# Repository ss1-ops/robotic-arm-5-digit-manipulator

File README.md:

# BCN3D Moveo Robotic Arm

Client-commissioned 6-DOF robotic arm (BCN3D Moveo base) with custom Aero Hand tendon-driven gripper. End goal: autonomous pick-and-place using computer vision on a Raspberry Pi running ROS 2 Jazzy, with low-level control on ESP32-S3 (micro-ROS).

**Current status (2026):** Transitioning from Arduino Uno R4 to ESP32-S3. Basic joint control, IK, and manual GUI working. Vision bring-up and full integration in progress. Aero Hand partially assembled (3 fingers functional).

## Quick Links
- [Current Build Status & Architecture](docs/arm-build-progress.md)
- [ROS 2 Setup on armpi (live inventory)](https://github.com/ss1-ops/robotic-arm-5-digit-manipulator/blob/main/docs/arm-build-progress.md) (see also Obsidian notes)
- [Aero Hand Gripper](gripper/aero-hand-open/) — full open-source tendon-driven hand (7 DoF, 3D-printed, ROS 2 + SDK + firmware)
- [Firmware (ESP32-S3)](firmware/esp32s3-arm-controller/)
- [Software / ROS 2 + GUI + Vision](software/)
- [Hardware / CAD](hardware/)
- [Original BCN3D Reference](reference/bcn3d-moveo/) (attribution + source files)

## Project Structure (Cleaned for Maintainability)
```
.
├── README.md
├── LICENSE
├── .gitattributes
├── docs/
│   └── arm-build-progress.md          # Detailed pinouts, commands, issues, future plans
├── hardware/
│   ├── cad/                           # Custom + reference CAD (STEP, STL, F3D, 3MF)
│   └── enclosure/                     # Custom platform/enclosure designs
├── firmware/
│   ├── esp32s3-arm-controller/        # Active micro-ROS target firmware
│   └── legacy-tests/                  # Earlier Arduino sketches
├── software/
│   ├── mac-gui/                       # macOS desktop GUI + ROS 2 nodes for manual control
│   ├── ros/                           # ROS 2 nodes, publishers, launchers
│   └── vision/                        # Stereo calibration, hand-eye, IBVS, object approach
├── gripper/
│   └── aero-hand-open/                # Full Aero Hand Open (tendon-driven EE)
│       ├── firmware/, hardware/ (CAD+PCB), ros2/, sdk/, ...
├── reference/
│   └── bcn3d-moveo/                   # Original open-source BCN3D Moveo mechanical files (parts 1+2)
├── urdf/                              # Robot description
└── assets/                            # Footage, images
```

## Current Capabilities
- ROS 2 Jazzy on Raspberry Pi (armpi.local)
- Joint control via forward_position_controller + serial bridge to stepper drivers
- Smooth IK + coordinated motion
- Manual Mac GUI for testing (joint sliders, sequences)
- Stereo vision pipeline (calibration, depth, object approach)
- Aero Hand gripper (tendon-driven, 7 servos, partial assembly + control)

See `docs/arm-build-progress.md` for pinouts, exact launch commands, known issues, and detailed roadmap (ESP32-S3 migration, PCA9685 for gripper, eye-in-hand CV, homing, etc.).

## Getting Started (High Level)
1. On the Pi: source ROS 2, launch description + controller.
2. Run serial bridge or micro-ROS agent.
3. Use Mac GUI or `ros2 topic pub` for commands.
4. For gripper: see `gripper/aero-hand-open/` (has its own SDK, ROS2 packages, firmware examples).

Full live setup details are in the build progress doc and the armpi SSH inventory.

## Sub-Projects & Highlights
- **Aero Hand Open** (`gripper/aero-hand-open/`): Professional open-source 7-DoF tendon-driven hand. Includes hardware (CAD, PCB, BOM), firmware, Python SDK, ROS 2 integration, simulation, RL tools. See its README for features, assembly, and shop links.
- **Vision & CV**: Hand-eye calibration, IBVS servo, stereo depth for pick-and-place. Eye-in-hand mount planned.
- **Firmware Evolution**: Moving to ESP32-S3 for native micro-ROS, OTA, more I/O (PCA9685 for servos, IMUs).

## License
MIT (see LICENSE). Sub-components may have their own licenses (e.g., Aero Hand, original BCN3D).

## Attribution
Base arm mechanics from the excellent open-source [BCN3D Moveo](https://github.com/BCN3D/BCN3D-Moveo) project. Custom work by Sam Snyder (automation, controls, integration, Aero Hand adaptation, vision).

For the absolute latest status, wiring, or Pi inventory, see the linked Obsidian notes or run live exploration on `armpi`.

---

**Active project** — contributions and questions welcome via issues or the linked Discord/community channels in the Aero Hand sub-project.

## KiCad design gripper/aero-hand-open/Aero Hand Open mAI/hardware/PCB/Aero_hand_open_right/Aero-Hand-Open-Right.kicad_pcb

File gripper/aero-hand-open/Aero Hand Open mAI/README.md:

<p align="center">

  <!--  -->

</p>

Aero Hand Open is an **open-source**, **tendon-driven** robotic hand designed and developed by TetherIA for dexterous manipulation research. Unlike expensive proprietary solutions, this hand focuses on **simplicity**, **reliability**, and **accessibility** by using standard 3D printing and off-the-shelf electronic components.

Each joint is optimized for mechanical efficiency through tendon actuation, enabling smooth and natural motion while maintaining a **lightweight** and **compact** design, making it perfect for research labs, educational institutions, and robotics enthusiasts who need an **affordable** yet **capable** manipulation platform.

> **📚 Learn More:** https://tetheria.github.io/aero-hand-open/   
> **🛒 Shop:** https://shop.tetheria.ai/

# Aero Hand Open features
- 7 DoFs robotic hand with 5 fingers (16 joints in total)
- Tendon-driven architecture for smooth and natural motion
- Fully 3D-printed structure, modular and easy to assemble
- Lightweight design — **389 g**
- Affordable — complete kit for **$314 USD**
- Open-source hardware and firmware
- Independent Python SDK, and compatible with ESP32 and ROS2 systems

# Table of Contents
- [Aero Hand Open features](#aero-hand-open-features)
- [Overview](#overview)
- [Resources](#resources)
  - [Bill of Materials (BOM)](#bill-of-materials-bom)
  - [CAD Files and 3D Models](#cad-files-and-3d-models)
  - [Assembly Guide](#assembly-guide)
  - [PCB Design](#pcb-design)
  - [Hardware Setup](#hardware-setup)
  - [Software SDK](#software-sdk)
  - [ROS2 and Teleoperation](#ros2-and-teleoperation)
  - [Simulation](#simulation)
  - [Reinforcement Learning](#reinforcement-learning-tools)
- [Getting help](#Getting-help)
- [License — TL;DR](#license--tldr)
- [Disclaimer](#disclaimer)
- [Project Updates & Community](#project-updates--community)
  - [Updates History](#updates-history)
  - [FAQ](#faq)
  - [Contact](#contact)

# Overview

# Resources
## Bill of Materials (BOM)
The complete list of components required to build Aero Hand Open can be found here:

 [👉 Aero Hand Open – Bill of Materials](./hardware/Assembly/BOM.csv)

This document includes all mechanical, electronic, and printed parts — such as motors, tendons, bearings, fasteners, and 3D-printed components.

Each item is listed with its part number, vendor, quantity, and estimated cost to help you easily source or substitute parts.

## CAD Files and 3D Models
STEP files and one click print files can be found here:

[👉 Aero Hand Open – CAD](./hardware/CAD/).

[👉 Aero Hand Open – Onshape Link](https://cad.onshape.com/documents/afc7e0ca7eb6d412ec8771f8/w/bc4d7e45e17e23d622d2bad2/e/c711982b7882da925263fb55?renderMode=0&uiState=6914cef580110c73012e8166)

All parts are printed on a Bambu X1C, 0.4mm nozzle, 0.2mm layer height, tree support enabled, select support on build plate only checkbox. We recommend keeping the same print orientation and settings. The print orientation will minimize supports and optimize surface tolerances/smoothness for interfacing components.

## Assembly Guide
The step-by-step assembly instructions for Aero Hand Open are provided in the following document:

[👉 Aero Hand Open – Assembly Guide](https://docs.tetheria.ai/docs/assembly)

This guide covers the entire build process, from mounting the actuators to routing the tendons and connecting the electronics. Each finger module can be assembled independently and attached to the palm afterward, allowing easier maintenance and quick replacement.

## PCB Design
All design files - including Gerber files, KiCad project files, BOM, and CPL - are available in [PCB folder](./hardware/PCB/).

Referring to [PCB doc](https://docs.tetheria.ai/docs/pcb) for more technical details.

## Hardware Setup

Please refer to [hardware_setup](https://docs.tetheria.ai/docs/hardware_setup) doc 

## Software SDK
Please refer to [`sdk/README.md`](sdk/README.md) and [sdk](https://docs.tetheria.ai/docs/sdk) doc

### Sequencing Demo
The Sequencing Demo demonstrates how different finger motions can be combined into continuous, pre-defined sequences.

This script enables users to perform complex gestures — such as pinching, opening the palm, or making a peace sign — by automatically coordinating joint movements in a timed sequence.

You can find the example code in the SDK example folder. 

👉 [`sdk/examples/`](sdk/examples)

Once the SDK is installed and the serial port has been configured, you can run any of the example scripts directly using Python as follows:

```bash
python run_sequence.py
```
[🎥 Watch the demo](assets/sequence_square.mp4)

## ROS2 and Teleoperation
The Aero Hand Open integrates seamlessly with ROS2 **humble** for advanced robotics applications.

Refer to the [ROS2](https://docs.tetheria.ai/docs/ros2) doc and [`ros2/`](./ros2/) folder for complete setup instructions and source code.

## Simulation

We provide high-fidelity simulation models for the **Tetheria Aero Hand Open**.

**Currently Supported**
- **MuJoCo**

Support for additional simulation platforms is under active development and will be released in future updates.  
Refer to the [RL and Sim](https://docs.tetheria.ai/docs/hand_sim) documentation and the [`sim_rl/simulation/`](./sim_rl/simulation/) directory for detailed explanations and model files.

## Reinforcement Learning Tools

We offer reinforcement learning tools built on top of state-of-the-art frameworks such as **mujoco_playground**, enabling users to train custom policies for the Aero Hand Open with minimal effort.

Refer to the [RL and Sim](https://docs.tetheria.ai/docs/hand_sim) documentation and the [`sim_rl/mujoco_playground/`](./sim_rl/mujoco_playground/) directory for full setup instructions and training procedures.  
An example of deploying trained policies in ROS is also provided in the [`ros2/`](./ros2/) directory.

# Getting help

**GitHub Issues** – Bugs + feature requests only.

**GitHub Discussions** –
- Build / electronics / mechanical help
- SDK / ROS2 / sim/RL "how do I…"
- Design proposals and feedback

**Discord** –
- Quick questions, live debugging, voice/screen‑share
- Social chat, lab intros, "I printed my first hand!"
- Live events and office hours

# License — TL;DR

- You **can** integrate Aero Hand units you purchase from TetherIA into **commercial robots and products** you sell.
- **Software (firmware & SDK):** Apache-2.0 — commercial use OK (with notices).
- **Design files (CAD/STEP/STL, drawings, BOM, docs):** CC BY‑NC‑SA 4.0 — **non‑commercial** only; derivatives must use the same license with attribution.
- Want to **manufacture/print parts** or **make your own hands** from our design files for commercial use (spares, kits, or clones)? → **Commercial manufacturing license required**.
- **Commercial licensing & volume buys:** see **LICENSE.md** (or email us at contact@tetheria.ai).

See [**LICENSE.md**](LICENSE.md) for definitions, examples, and contact details.

© 2025 TetherIA Inc. All rights reserved.

# Disclaimer
Aero Hand Open is an open-source research prototype intended for educational and experimental purposes only.

While every effort has been made to ensure build accuracy and functionality, this design has not been validated for prolonged or heavy-duty use.

Users should exercise caution when assembling, operating, or modifying this device. TetherIA Inc. and its contributors shall not be held liable for any personal injury, property damage, or other losses resulting from the use, misuse, or modification of this design. By using this project, you acknowledge and accept full responsibility for any associated risks.

Important Notes:
- 3D-printed parts may exhibit tolerance variations depending on printer and material settings.
- The tendon-driven mechanism requires regular tension adjustment to maintain consistent motion.
- Overloading the joints or applying excessive torque may cause mechanical deformation or servo damage.
- This project is provided as is, without any warranty or guarantee of fitness for a particular purpose.

We encourage the community to share improvements, feedback, and modifications through pull requests or GitHub discussions.

Your contributions will help make Aero Hand Open more reliable and versatile for the entire robotics community.

# Project Updates & Community
## Updates History
See [RELEASE_NOTES.md](RELEASE_NOTES.md) for details.

## FAQ
Q1: Can I modify and redistribute the Aero Hand Open design?

A: Yes, as long as it complies with the CC BY-NC-SA 4.0 license (non-commercial, attribution required, share alike).

Q2: What 3D printer and material do you recommend?

A: Any FDM printer with a ≥200×200 mm bed. PLA works best for strength and dimensional accuracy.

More questions please refer to our [online documentation](https://docs.tetheria.ai/docs/hardware_faq) 

## Contact
For questions, feedback, or collaboration inquiries, please reach out to us through the following channels:

 🛒 Shop: [Aero Hand Open – TetherIA Store](https://shop.tetheria.ai/) 

 📚 Docs: [TetherIA Docs](https://docs.tetheria.ai/)

 📧 Email: support@tetheria.ai

 🌐 Website: [tetheria.ai](http://tetheria.ai)

 🐙 GitHub: [TetherIA](https://github.com/TetherIA)

 💬 Discord: [TetherIA Discord Channel](http://discord.gg/ZQKWK7NebQ)

  🐦 X/Twitter: [TetherIA X/Twitter Account](https://x.com/TetherIA_ai)

  📺 YouTube: [TetherIA YouTube Account](https://www.youtube.com/@TetherIA_ai)

  💼 LinkedIn: [TetherIA LinkedIn Account](https://www.linkedin.com/company/tetheria/)

We welcome discussions, contributions, and new ideas from the community.

If you have improvements to the design, firmware, or control software, feel free to open a Pull Request or start a Discussion on GitHub.

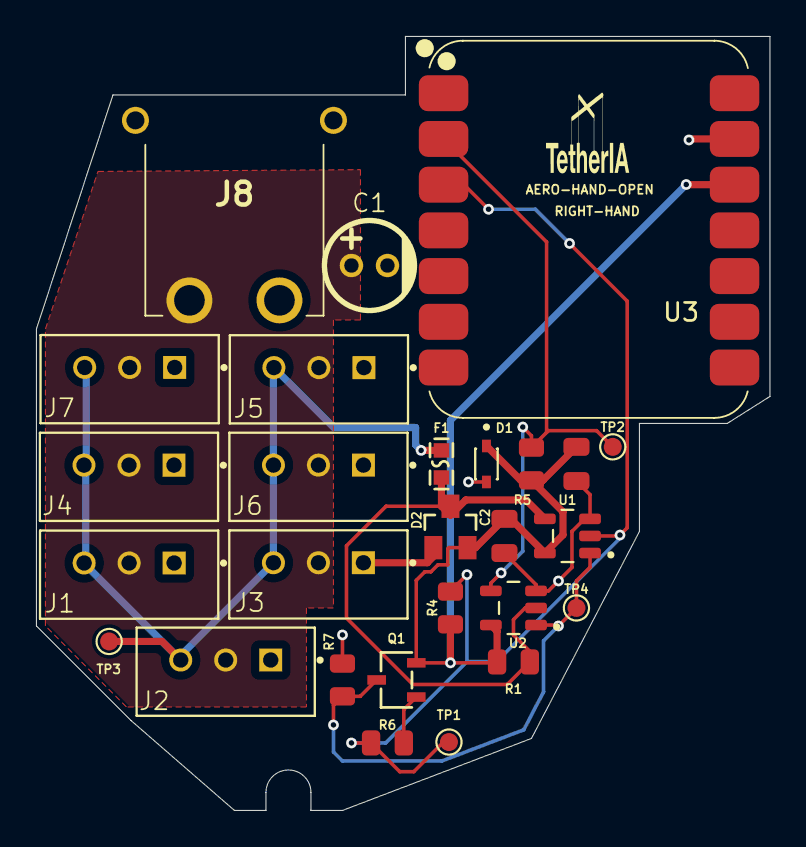
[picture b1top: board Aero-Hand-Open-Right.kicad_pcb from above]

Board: 2 copper layers, 40.7 x 43.0 mm, 27 parts (1 on the bottom side), 9 nets.

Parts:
C1: 100uF; CAP-TH_BD5.0-P2.00-D0.8-FD
C2, C3: 0.1uF; C_0805
D1: BZT52B5V1S; DIO_BZT52B5V1S
D2: BAT54S; bat4s kl4
F1: BSMD0603-010-24V; F0603
J1, J2, J3, J4, J5, J6, J7: 22-03-5035; MOLEX_22-03-5035
J8: XT30PW-M; XT30PWM
Q1: MMBT2907A; transistor-SOT-23-3_L3.0-W1.7-P0.95-LS2.9-BR
R1, R4, R5: 10K; R_0805
R6: 1K; R_0805
R7: 3.3K; R_0805
TP1, TP2, TP3, TP4: TestPoint; TestPoint_Pad_D1.0mm
U1: SN74LVC1G126DBVR
U2: SN74LVC1G125DBVR
U3: XIAO-ESP32-S3-DIP; XIAO-ESP32S3-SMD

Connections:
DC6V: C1.1, J1.2, J2.2, J3.2, J4.2, J5.2, J6.2, J7.2, J8.2
GND: C1.2, C2.1, C3.1, D1.A, D2.1, J1.1, J2.1, J3.1, J4.1, J5.1, J6.1, J7.1, J8.1, J8.3, J8.4, R7.2, U1.3 (GND), U2.3 (GND), U3.13 (GND)
unnamed: Q1.1 (B), R6.2
Servo_DATA: D2.3, F1.2, R1.1, U1.4 (Y), U2.2 (A)
Servo_DATA_IN: F1.1, J1.3, J2.3, J3.3, J4.3, J5.3, J6.3, J7.3, TP3.1
Servo_RXD: R4.2, R6.1, TP1.1, U1.2 (A), U3.3 (GPIO3/A2/D2)
Servo_RXEN: Q1.3 (C), R7.1, TP4.1, U1.1 (OE), U2.1 (~OE)
Servo_TXD: R5.2, TP2.1, U2.4 (Y), U3.2 (GPIO2/A1/D1)
VCC: C2.2, C3.2, D1.C, D2.2, Q1.2 (E), R1.2, R4.1, R5.1, U1.5 (VDD), U2.5 (VCC), U3.12 (VCC_3V3)

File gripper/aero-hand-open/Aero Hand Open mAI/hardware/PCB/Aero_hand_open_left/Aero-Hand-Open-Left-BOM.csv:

Comment,Quantity,Designator,Footprint,JLCPCB Part,Link,,,,,,,,,,,,,,
100uF,1,C1,CAP-TH_BD5.0-P2.00-D0.8-FD,C47873,https://jlcpcb.com/partdetail/48879-KM107M025D11RR0VH2FP0/C47873,,,,,,,,,,,,,,
100nF,2,"C2,C3",C_0805,C520082,https://jlcpcb.com/partdetail/YAGEO-CC0805JRX7R7BB104/C520082,,,,,,,,,,,,,,
BZT52B5V1S,1,D1,DIO_BZT52B5V1S,C5261067,https://jlcpcb.com/partdetail/HXYMOSFET-BZT52B5V1S/C5261067,,,,,,,,,,,,,,
BAT54S,1,D2,BAT4S KL4,C8592,https://jlcpcb.com/partdetail/9087-BAT54SKL4/C8592,,,,,,,,,,,,,,
BSMD0603-010-24V,1,F1,F0603,C883089,https://jlcpcb.com/partdetail/BHFUSE-BSMD0603_01024V/C883089,,,,,,,,,,,,,,
MOLEX CONNECTOR,7,"J1,J2,J3,J4,J5,J6,J7",MOLEX_22-03-5035,C5458299,https://jlcpcb.com/partdetail/MOLEX-0022035053/C5458299,,,,,,,,,,,,,,
XT30PW-M,1,J8,XT30PWM,C431092,https://jlcpcb.com/partdetail/Changzhou_AmassElec-XT30PW_M30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,,,,,,,,,,,,,,
MMBT2907A,1,Q1,Transistor-SOT-23-3_L3.0-W1.7-P0.95-LS2.9-BR,C305431,https://jlcpcb.com/partdetail/Foshan_Blue_RocketElec-MMBT290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,,,,,,,,,,,,,,
10K,3,"R1,R4,R5",R_0805,C702829,https://jlcpcb.com/partdetail/HKR_Hong_Kong_Resistors-RCT051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,,,,,,,,,,,,,,
1K,1,R6,R_0805,C702831,https://jlcpcb.com/partdetail/HKR_Hong_Kong_Resistors-RCT051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,,,,,,,,,,,,,,
3.3K,1,R7,R_0805,C702834,https://jlcpcb.com/partdetail/HKR_Hong_Kong_Resistors-RCT053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,,,,,,,,,,,,,,
SN74LVC1G126DBVR,1,U1,SN74LVC1G126DBVR,C7834,https://jlcpcb.com/partdetail/TexasInstruments-TISN74LVC1G12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,,,,,,,,,,,,,,
SN74LVC1G125DBVR,1,U2,SN74LVC1G125DBVR,C23654,https://jlcpcb.com/partdetail/TexasInstruments-TISN74LVC1G12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,,,,,,,,,,,,,,

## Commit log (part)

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2026-04-10 Initial project import
2026-04-10 Add Aero Hand Open mAI project
2026-04-23 Rename ESP32-S3 arm controller sketch
2026-04-24 working micro_ros over UDP
2026-04-25 simple GUI controller + shift stepper pins to 3-12
2026-05-06 Fix homing: use Float32 for /home_cmd, fix reconnect cleanup loop
2026-05-06 Fix coordinated motion: time-based pacemaker, raise RAMP_MIN_V to 0.25
2026-05-06 Two-zone table collision floor: z>=-0.1m when r>0.14m, else z>=0.14m
2026-05-06 Fix micro-ROS: spin_some timeout 0→1ms, passive watchdog, no double-cleanup, init watchdog on connect
2026-05-07 Fix ramp: correct comments to trapezoidal, set accel/decel fracs to 7.5%
2026-05-07 Switch micro-ROS transport from WiFi UDP to USB CDC
    Firmware (esp32s3_arm_controller.ino):
    - Replace set_microros_wifi_transports(...) with set_microros_transports();
    Serial (= USB CDC under CDCOnBoot=cdc) is now the XRCE-DDS transport.
    - Drop WiFi.h, WebServer.h, ESPmDNS.h, ElegantOTA.h and all related state.
    - Remove every Serial.print* call; with Serial as the transport any debug
    byte would corrupt the protocol stream.
2026-05-07 Add /reboot topic for remote ESP32 restart
    The reset button on the dev board is too small to reliably solder a GPIO
    wire to, so add a software-side path: publish data >= 0.5 to /reboot
    and the ESP32 calls ESP.restart() after a 100ms ack-grace delay.
    ros2 topic pub --once /reboot std_msgs/msg/Float32 "{data: 1.0}"
    Tested: chip rebooted, USB CDC re-enumerated, agent saw the old session
    close and a new session establish under a different client_key in ~7 s,
2026-06-02 Vision: GUI auto-start, upside-down recalibration, hand-eye attempt + IBVS pivot
    GUI (moveo_simple_controller.py): Connect SSH now also starts the vision stack
    (camera + MJPEG browser stream) via Vision/pi/start_vision.sh.
    Camera mounted upside down: software flip can't recover the upright calibration's
    stereo rectification (swaps physical L/R; rectification is role-specific). Driver
    streams raw frames (rotate_180=false), stream display-rotates for viewing only.
    Added on-Pi recalibration (capture_stereo_pi.py) for the as-mounted orientation;
2026-06-02 IBVS point-at-object working: pixel visual servoing + joint probe
    Pivot from hand-eye (infeasible on open-loop arm) to image-based visual servoing,
    which closes the loop on the camera and is immune to the arm's FK / reversed /
    mis-scaled joints because it measures the joint->image relationship online.
    - ibvs_servo.py: detects checkerboard centroid in the raw left image, estimates a
    2x2 d(u,v)/dq Jacobian (j1 yaw / j5 pitch) by jogging, then servos the centroid
    to image centre via damped least squares. Converged in 3 steps (109->22px) on
2026-06-02 Approach servo: smoothness tune (Broyden Jacobian update + gentler gain/damping)
    Online Broyden rank-1 update keeps the Jacobian current as the arm extends during
    approach (the centring response changes with reach), removing the servo
    oscillation. Lower gain (0.25) + higher DLS damping (20). Result: monotonic
    convergence, no sign-flips, 4 steps (vs 13).
2026-06-02 Kinematics: real link lengths in ikpy chain + clean URDF
    (a) moveo_publisher.py MOVEO_CHAIN updated with real link lengths from the CAD
    URDF joint-to-joint distances (base->J1 0.13, J1->J2 0.183, J2->J3 0.221,
    J3->J4 0.170, J4->J5 0.053), replacing approximate guesses. Adds the previously-
    missing waist (j2) and wrist (j5) segments (were zero offset). EE at home now
    (0,0,0.797), clean vertical stack. Should reduce the residual hand-eye FK error.
    Live file installed on the Pi (backup: moveo_publisher.py.bak-20260602).
2026-06-02 hand-eye: ChArUco support (removes planar pose-rotation ambiguity)
    The plain checkerboard's solvePnP rotation flips between two near-equal solutions
    on near-frontal views (low reproj doesn't catch it), corrupting hand-eye's rotation
    inputs -> the stuck ~200mm residual / bogus 27cm T_ee_cam. ChArUco's embedded ArUco
    markers fix orientation -> unambiguous pose.
    - make_charuco.py: generate a printable 7x5 ChArUco (DICT_4X4_50, 28mm sq nominal).
    - hand_eye_calibrate.py: refactor detection into _detect_pose() supporting both
2026-06-03 Fix ESP USB transport, IK frame/seeding, j4 dir; add camera mount
    Firmware:
    - Reverse j4 (wrist roll) direction (DIR_INVERT[3]=false) per measured behaviour.
    ESP flashing (root-caused a total micro-ROS comms loss):
    - flash_esp32_from_pi.sh: FQBN was missing :CDCOnBoot=cdc, which routed Serial
    (the micro-ROS transport) to UART0 pins instead of USB -> agent saw silence.
    Also fixed stale agent baud (115200) and port (/dev/ttyACM0).
2026-06-03 Reliable approach seeding + GUI connects by IP
    - moveo_publisher: re-publish the last /joint_commands at 2Hz (gated until the
    first real command). The topic is VOLATILE, so the approach servo (launched on
    a GUI click, after a command) would wait forever for the next send; re-publishing
    lets it grab the current pose as soon as it subscribes. During a servo it just
    echoes the latest jog command (no conflict). Verified: approach reaches the
    Jacobian step with no second send.
2026-06-03 depth: blob-median fallback for solid objects (fix BEARING_ONLY)
    A uniform/glossy colour blob has no stereo disparity in its interior, so sampling
    depth at the centroid returned nothing -> BEARING_ONLY -> the servo saw no target.
    When the centroid window has no depth, fall back to the median 3D point over all
    valid-depth pixels inside the colour mask (the blob's textured edges carry depth).
2026-06-03 goto_object: stable centering (median measure) + reach clamp
    - _measure now returns the median of N TRACK frames instead of a single frame.
    A single noisy depth frame was jumping the centering offset (6.7->18.6cm) and
    stalling the servo; with the object then uncentered, the lateral term got applied
    outside the optical axis -> the 'weird' estimated location.
    - Clamp the cartesian target to the arm's reach (from the J1 axis): if the object
    is beyond reach, approach toward it to the limit instead of failing IK outright,
2026-06-04 goto_object: incremental approach with camera re-aiming between steps
    Single cartesian jump was letting IK pick a j5 that reached the target position
    but didn't keep the camera aimed at the object -> lost visibility immediately.
    New flow:
    1. Initial center (j1/j5 IBVS as before)
    2. Compute object position from FK + camera mount
    3. Incremental approach: move approach_step_m (default 6cm) toward the object,
2026-06-04 GUI: kill all vision procs on Connect (prevent duplicate camera nodes)
    Each Connect click was spawning a new camera+stream on top of old ones because
    _CMD_KILL only killed the agent and publisher. Two stereo_camera_nodes fighting
    /dev/video0 => load 5.9, 2.3fps, depth node starved => NONE detections.
    Now kills camera, depth, stream, goto_object, approach_object too.
2026-06-04 GUI: wider HSV tolerance for color detection (fix stream-vs-depth mismatch)
    JPEG compression + rectification/resize in the depth node shifts colors vs the
    raw MJPEG stream the GUI samples from. dh 12->18, looser s/v floor to survive
    the pipeline's color shift.
2026-06-04 goto_object: fix Q matrix scaling (use stereoRectify at scaled K, not manual)
    My _load_cal was manually scaling Q incorrectly: it didn't scale Q[0,3]/Q[1,3]/Q[3,3]
    and wrongly divided Q[3,2] (baseline term). This caused reprojectImageTo3D to compute
    wrong depths (roughly 2x off) and wrong X/Y positions.
    Fix: scale K1/K2 by 0.5, call cv2.stereoRectify at the scaled size — same as what
    stereo_depth_node.py does. OpenCV then returns the correctly-scaled Q directly.
    Also add tan(j1) vs actual y/x diagnostic to the estimated-location log line so we
2026-06-04 goto_object: pin j1/j2/j4 from centered pose, only j3 changes on approach
    IK was jumping configurations (j2: 0->1.676) causing 103-degree j5 corrections
    and unpredictable motion. After centering we already know j1 (horizontal aim)
    and the shoulder is at j2=0. Only j3 (arm extension/depth) should change to
    approach the object. Force j1=centered, j2=centered, j4=0, use IK's j3 only.
2026-06-05 docs: major README rewrite and project structure documentation for presentability
2026-06-05 chore: add MIT LICENSE at root
2026-06-05 refactor: remove old root clutter (reorganized locally to hardware/cad/)
2026-06-05 refactor: remove old root clutter (reorganized locally to docs/)
2026-06-05 refactor: remove old root clutter (reorganized locally to reference/)
2026-06-06 chore: flatten Aero Hand subproject one level inside gripper/aero-hand-open/
2026-06-08 feat(F-006): light reconnect by default (leave micro_ros_agent running persistently)
    - _CMD_KILL now "cleanup": /reboot + pkill only non-agent nodes + report tty holders (no killall agent, no fuser -k, no re-enum)
    - _CMD_AGENT now "ensure": if already running print it (persistent), else start
    - Removed tail -5 /tmp/mra.log from ESP32 poll (no more raw colored ProxyClient subscriber/datareader lines dumped into GUI startup log)
    - Safe printf > /tmp/ + bash for both (single-line cmd to paramiko to avoid shlex/quoting "bash: -c: line 2: syntax error: unexpected end of file")
    - test_reconnect_after_kill.sh updated with --light + matching no-tail
    Tested: python extract live _CMD_* + shlex + dire
2026-06-08 feat(kinematics): unify FK/IK with single source of truth in kinematics.py + corrected lengths (BASE=0.20, WAIST=0.140, UPPER=0.22, FORE=0.11, WRIST=0.11, EE=0.06)
    - Make software/mac-gui/kinematics.py the canonical definition (lengths + Chain).
    - Update both moveo_publisher.py (Mac + Pi) to use it (import on Mac, try-import + fallback on Pi).
    - Fix user-frame convention: forward_kinematics now returns +X forward / +Y left so Compute FK button matches IK targets.
    - Correct 2R pre-solve for non-zero WAIST.
    - Pi TCP response now includes 'achieved' (user-frame) for immediate verification in logs.
    - Higher angle precision on wire + safer restart in deploy.
2026-06-09 feat: offload full vision processing to Mac + integrate into GUI
    - Port complete goto_object/approach logic (blob detect, SGBM depth, centering with j1/j5, object pose, IK target, j5 aim, verify) to run on Mac using pure kinematics.
    - New Mac helpers: mac_stereo_grabber.py (HTTP /left /right from Pi stream), mac_processor.py (demo depth), mac_goto_object.py (full ported class with callbacks for GUI).
    - Integrate 'Vision Approach (Mac offload)' controls + 'Start Approach' button into moveo_simple_controller.py GUI. Uses existing TCP for commands, polls Pi stream for frames. Reuses camera preview i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
    - Enhance Pi mjpeg_stream.py to serve high-quality /left and /right JPEGs (for Mac
